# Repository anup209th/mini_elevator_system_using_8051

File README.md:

# mini_elevator_system_using_8051
A mini elevator system for 5 floors using the C8051F3BC-GM microcontroller and L293D motor driver. Designed in KiCad with schematic and PCB layout. Features bidirectional motor control, GPIO-based logic, and floor indication via LEDs. Ideal for embedded systems practice.

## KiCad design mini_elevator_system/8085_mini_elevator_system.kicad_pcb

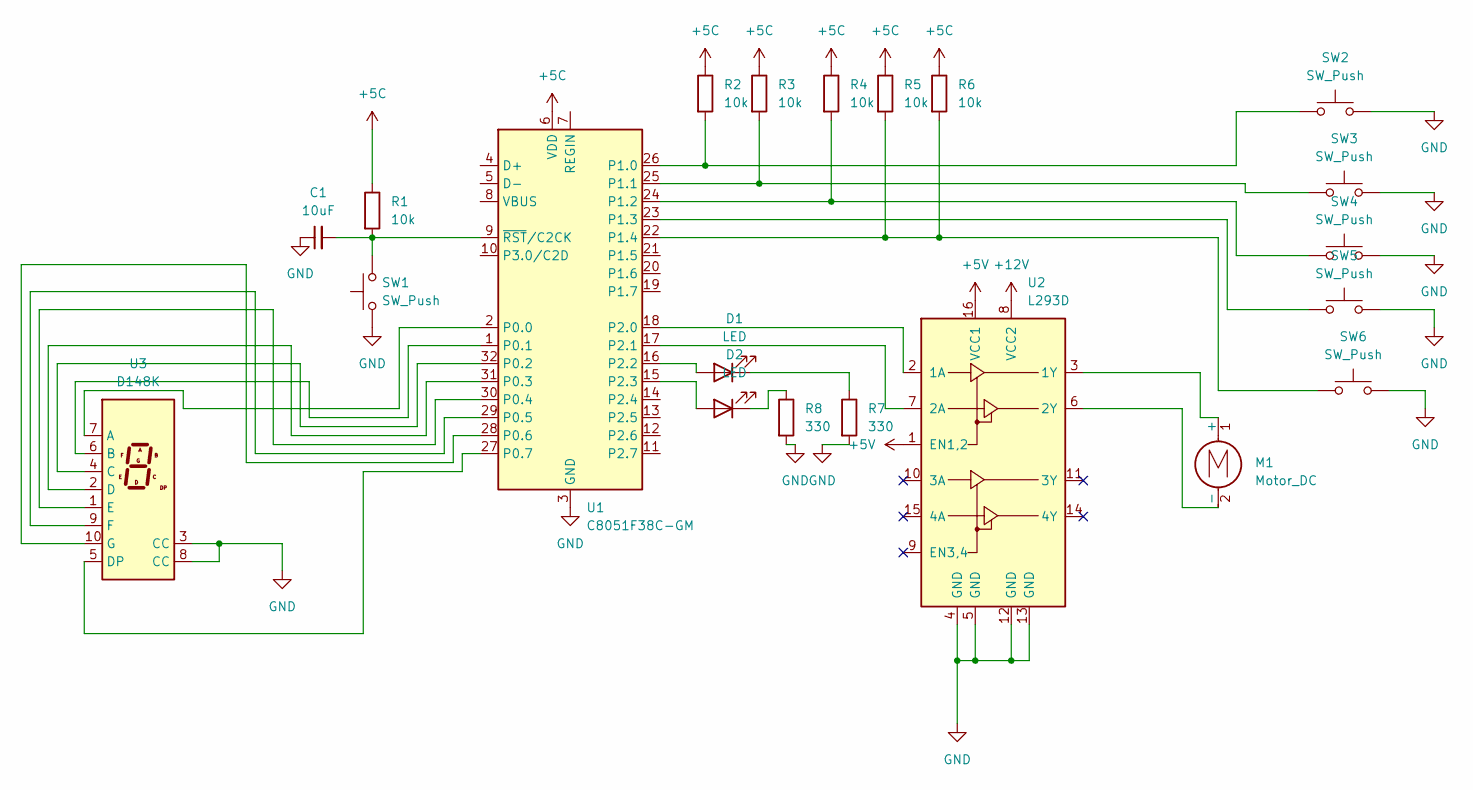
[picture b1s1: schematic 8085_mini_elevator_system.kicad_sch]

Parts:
C1: 10uF
D1, D2: LED
M1: Motor_DC
R1, R2, R3, R4, R5, R6: 10k
R7, R8: 330
SW1, SW2, SW3, SW4, SW5, SW6: SW_Push
U1: C8051F38C-GM; QFN-32-1EP_5x5mm_P0.5mm_EP3.3x3.3mm
U2: L293D; DIP-16_W7.62mm
U3: D148K; D1X8K

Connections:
+5C: R1.1, R2.1, R3.1, R4.1, R5.1, R6.1, U1.6 (VDD)
+5V: U2.1 (EN1,2), U2.16 (VCC1); also elsewhere on the board
+12V: U2.8 (VCC2); also elsewhere on the board
GND: C1.1, R7.2, R8.2, SW1.1, SW2.2, SW3.2, SW4.2, SW5.2, SW6.2, U1.3 (GND), U1.33 (GND), U2.4 (GND), U2.5 (GND), U2.12 (GND), U2.13 (GND), U3.3 (CC), U3.8 (CC); also elsewhere on the board
unnamed: D1.2 (A), U1.16 (P2.2)
unnamed: D1.1 (K), R7.1
unnamed: D2.2 (A), U1.15 (P2.3)
unnamed: D2.1 (K), R8.1
unnamed: M1.1 (+), U2.3 (1Y)
unnamed: M1.2 (-), U2.6 (2Y)
unnamed: U1.2 (P0.0), U3.7 (A)
unnamed: U1.1 (P0.1), U3.6 (B)
unnamed: U1.32 (P0.2), U3.4 (C)
unnamed: U1.31 (P0.3), U3.2 (D)
unnamed: U1.30 (P0.4), U3.1 (E)
unnamed: U1.29 (P0.5), U3.9 (F)
unnamed: U1.28 (P0.6), U3.10 (G)
unnamed: U1.27 (P0.7), U3.5 (DP)
unnamed: R2.2, SW2.1, U1.26 (P1.0)
unnamed: R3.2, SW3.1, U1.25 (P1.1)
unnamed: R4.2, SW4.1, U1.24 (P1.2)
unnamed: SW5.1, U1.23 (P1.3)
unnamed: R5.2, R6.2, SW6.1, U1.22 (P1.4)
unnamed: U1.18 (P2.0), U2.2 (1A)
unnamed: U1.17 (P2.1), U2.7 (2A)
unnamed: C1.2, R1.2, SW1.2, U1.9 (~RST/C2CK)

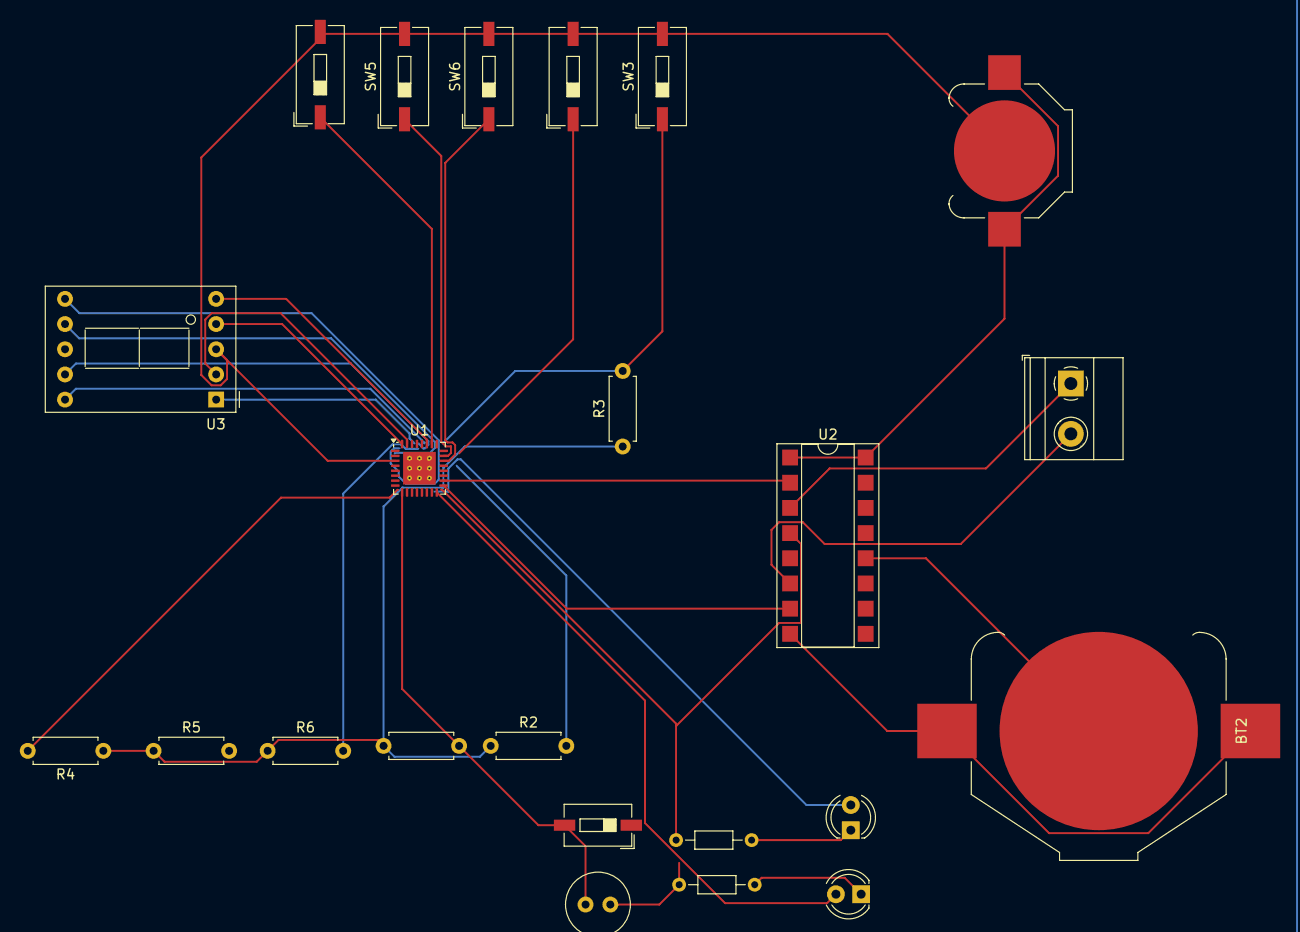
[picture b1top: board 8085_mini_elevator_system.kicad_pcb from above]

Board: 2 copper layers, 23 parts (0 on the bottom side), 26 nets.

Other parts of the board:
BT1: Battery_Cell; BatteryHolder_Keystone_3000_1x12mm
BT2: Battery_Cell; BatteryHolder_Keystone_3008_1x2450

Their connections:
+5V: BT1.1 (+); also elsewhere on the board
+12V: BT2.1 (+); also elsewhere on the board
GND: BT1.2 (-), BT2.2 (-); also elsewhere on the board
